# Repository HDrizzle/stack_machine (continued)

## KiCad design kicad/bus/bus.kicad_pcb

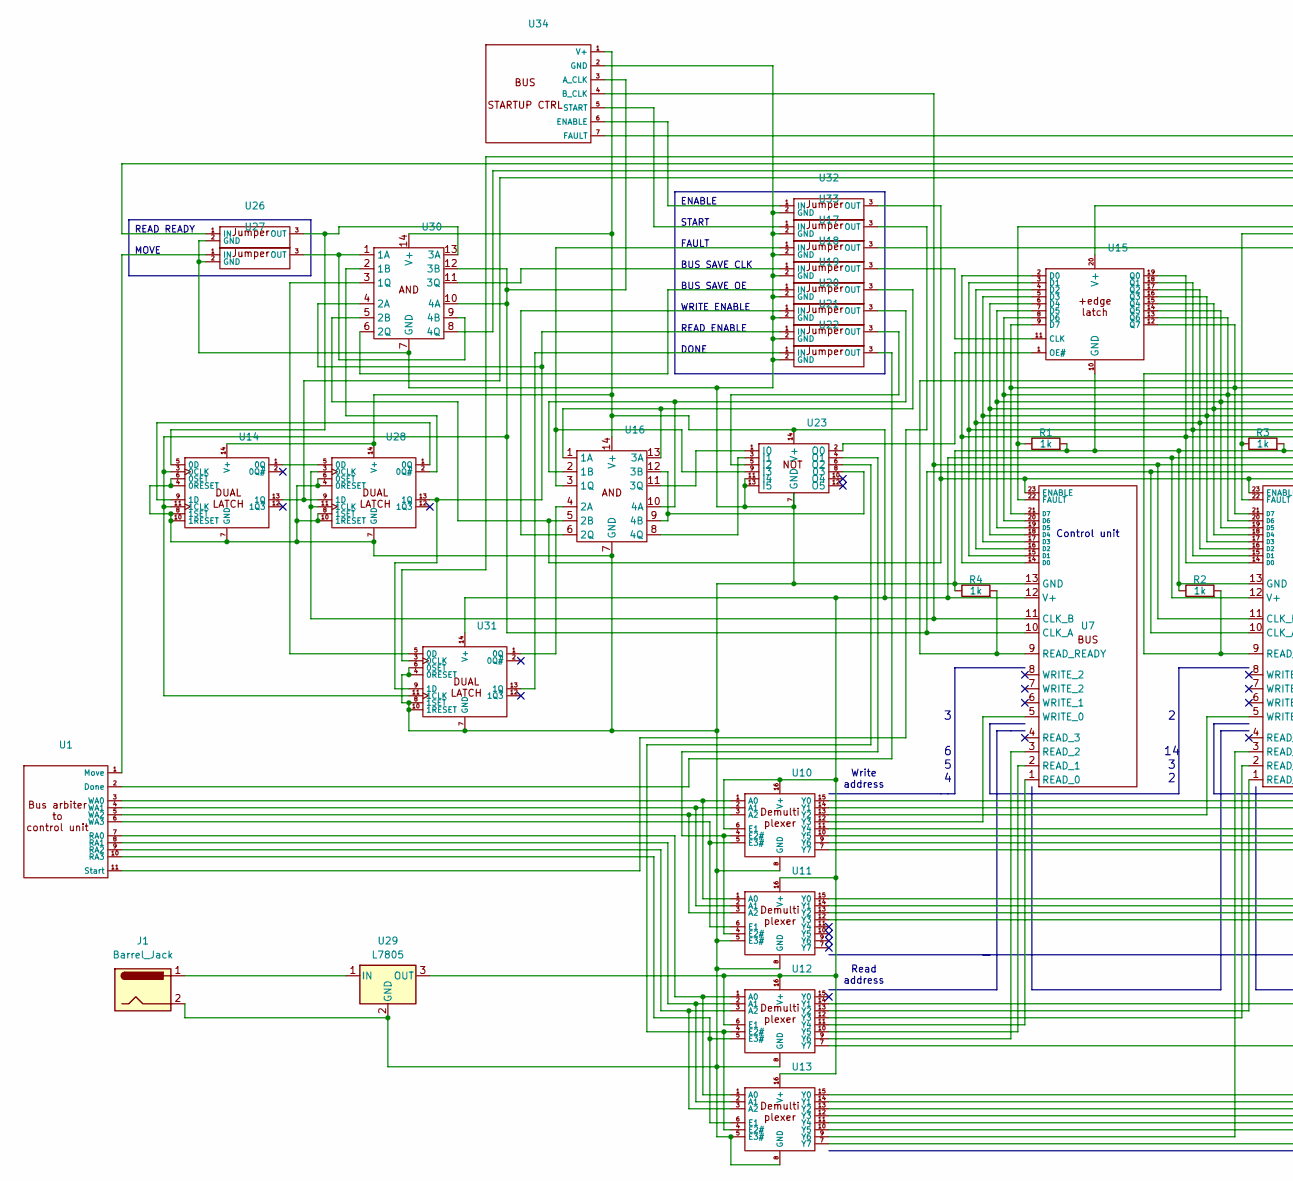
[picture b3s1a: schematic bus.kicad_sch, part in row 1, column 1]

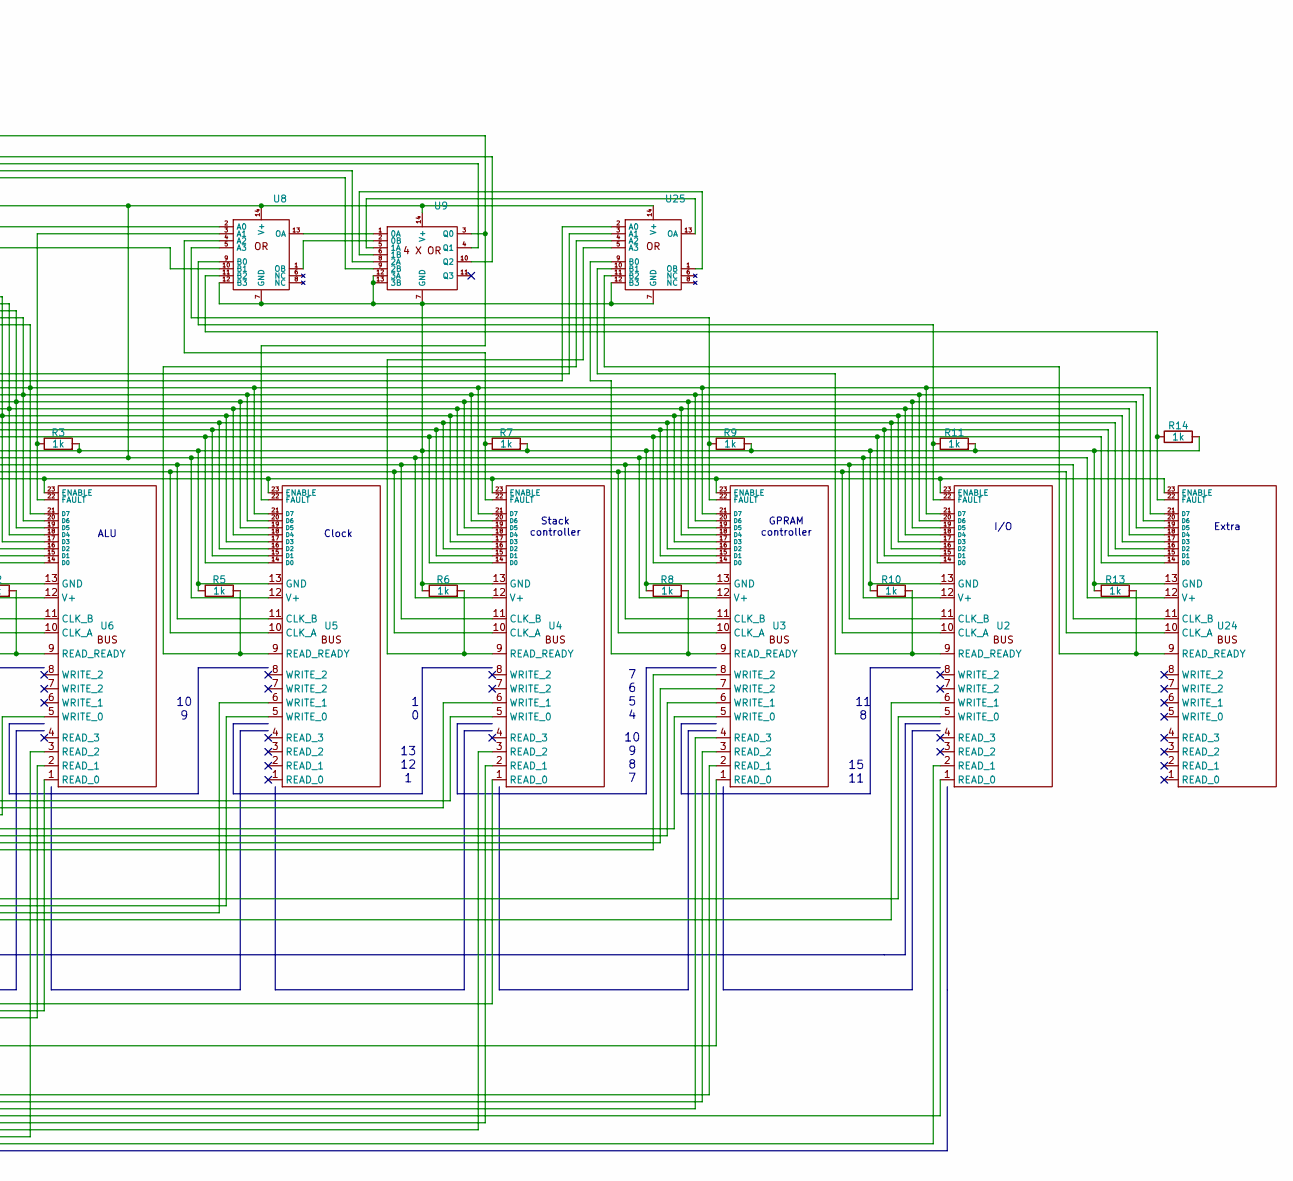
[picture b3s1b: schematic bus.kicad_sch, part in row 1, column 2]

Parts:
J1: Barrel_Jack; BarrelJack_Horizontal
R1, R2, R3, R4, R5, R6, R7, R8, R9, R10, R11, R13, R14: 1k; 0.4_pitch_resistor
U1: PinHeader_1x11_P2.54mm_Vertical
U2, U3, U4, U5, U6, U7, U24: PinHeader_1x23_P2.54mm_Vertical
U8, U9, U14, U16, U23, U25, U28, U30, U31: DIP-14_W7.62mm
U10, U11, U12, U13: DIP-16_W7.62mm
U15: DIP-20_W7.62mm
U17, U18, U19, U20, U21, U22, U26, U27, U32, U33: jumper
U29: L7805; TO-220-3_Vertical
U34: PinHeader_1x07_P2.54mm_Vertical

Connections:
unnamed: U1.2 (Done), U22.3 (OUT)
unnamed: U1.1 (Move), U27.1 (IN)
unnamed: U1.7 (RA0), U12.1 (A0), U13.1 (A0)
unnamed: U1.8 (RA1), U12.2 (A1), U13.2 (A1)
unnamed: U1.9 (RA2), U12.3 (A2), U13.3 (A2)
unnamed: U1.10 (RA3), U12.5 (E3#), U13.6 (E1)
unnamed: U1.11 (Start), U33.3 (OUT)
unnamed: U1.3 (WA0), U10.1 (A0), U11.1 (A0)
unnamed: U1.4 (WA1), U10.2 (A1), U11.2 (A1)
unnamed: U1.5 (WA2), U10.3 (A2), U11.3 (A2)
unnamed: U1.6 (WA3), U10.5 (E3#), U11.6 (E1)
unnamed: U2.11 (CLK_B), U3.11 (CLK_B), U4.11 (CLK_B), U5.11 (CLK_B), U6.11 (CLK_B), U7.11 (CLK_B), U24.11 (CLK_B), U28.3 (0CLK), U28.11 (1CLK), U34.4 (B_CLK)
unnamed: R11.1, U2.22 (FAULT), U8.9 (B0)
unnamed: R10.2, U2.9 (READ_READY), U25.10 (B1)
unnamed: R9.1, U3.22 (FAULT), U8.5 (A3)
unnamed: R7.1, U4.22 (FAULT), U8.4 (A2)
unnamed: R3.1, U6.22 (FAULT), U8.3 (A1)
unnamed: R1.1, U7.22 (FAULT), U8.2 (A0)
unnamed: U8.13 (OA), U9.1 (0A)
unnamed: U8.1 (OB), U9.2 (0B)
unnamed: U2.12 (V+), U3.12 (V+), U4.12 (V+), U5.12 (V+), U6.12 (V+), U7.12 (V+), U8.14 (V+), U9.14 (V+), U10.6 (E1), U10.16 (V+), U11.16 (V+), U12.6 (E1), U12.16 (V+), U13.16 (V+), U14.14 (V+), U15.20 (V+), U16.14 (V+), U23.14 (V+), U24.12 (V+), U25.14 (V+), U28.14 (V+), U29.3 (OUT), U30.14 (V+), U31.14 (V+), U34.1 (V+)
unnamed: U10.4 (E2#), U11.4 (E2#), U23.4 (O1)
unnamed: J1.2, R1.2, R2.1, R3.2, R4.1, R5.1, R6.1, R7.2, R8.1, R9.2, R10.1, R11.2, R13.1, R14.2, U2.13 (GND), U3.13 (GND), U4.13 (GND), U5.13 (GND), U6.13 (GND), U7.13 (GND), U8.7 (GND), U8.12 (B3), U9.7 (GND), U9.12 (3A), U9.13 (3B), U10.8 (GND), U11.5 (E3#), U11.8 (GND), U12.8 (GND), U13.5 (E3#), U13.8 (GND), U14.4 (0RESET), U14.6 (0SET), U14.7 (GND), U14.8 (1SET), U14.10 (1RESET), U15.10 (GND), U16.7 (GND), U17.2 (GND), U18.2 (GND), U19.2 (GND), U20.2 (GND), U21.2 (GND), U22.2 (GND), U23.7 (GND), U23.11 (I4), U23.13 (I5), U24.13 (GND), U25.7 (GND), U25.12 (B3), U26.2 (GND), U27.2 (GND), U28.4 (0RESET), U28.6 (0SET), U28.7 (GND), U28.8 (1SET), U28.10 (1RESET), U29.2 (GND), U30.7 (GND), U31.4 (0RESET), U31.6 (0SET), U31.7 (GND), U31.8 (1SET), U31.10 (1RESET), U32.2 (GND), U33.2 (GND), U34.2 (GND)
unnamed: U4.5 (WRITE_0), U10.15 (Y0)
unnamed: U4.6 (WRITE_1), U10.14 (Y1)
unnamed: U6.5 (WRITE_0), U10.13 (Y2)
unnamed: U7.5 (WRITE_0), U10.12 (Y3)
unnamed: U3.5 (WRITE_0), U10.11 (Y4)
unnamed: U3.6 (WRITE_1), U10.10 (Y5)
unnamed: U3.7 (WRITE_2), U10.9 (Y6)
unnamed: U3.8 (WRITE_2), U10.7 (Y7)
unnamed: U2.5 (WRITE_0), U11.15 (Y0)
unnamed: U5.5 (WRITE_0), U11.14 (Y1)
unnamed: U5.6 (WRITE_1), U11.13 (Y2)
unnamed: U2.6 (WRITE_1), U11.12 (Y3)
unnamed: U12.4 (E2#), U13.4 (E2#), U23.6 (O2)
unnamed: U4.1 (READ_0), U12.14 (Y1)
unnamed: U6.1 (READ_0), U12.13 (Y2)
unnamed: U6.2 (READ_1), U12.12 (Y3)
unnamed: U7.1 (READ_0), U12.11 (Y4)
unnamed: U7.2 (READ_1), U12.10 (Y5)
unnamed: U7.3 (READ_2), U12.9 (Y6)
unnamed: U3.1 (READ_0), U12.7 (Y7)
unnamed: U3.2 (READ_1), U13.15 (Y0)
unnamed: U3.3 (READ_2), U13.14 (Y1)
unnamed: U3.4 (READ_3), U13.13 (Y2)
unnamed: U2.1 (READ_0), U13.12 (Y3)
unnamed: U4.2 (READ_1), U13.11 (Y4)
unnamed: U4.3 (READ_2), U13.10 (Y5)
unnamed: U6.3 (READ_2), U13.9 (Y6)
unnamed: U2.2 (READ_1), U13.7 (Y7)
unnamed: U2.10 (CLK_A), U3.10 (CLK_A), U4.10 (CLK_A), U5.10 (CLK_A), U6.10 (CLK_A), U7.10 (CLK_A), U14.3 (0CLK), U14.11 (1CLK), U24.10 (CLK_A), U30.10 (4A), U30.12 (3B), U31.11 (1CLK), U34.3 (A_CLK)
unnamed: U14.5 (0D), U26.3 (OUT), U30.13 (3A)
unnamed: U14.1 (0Q), U28.5 (0D)
unnamed: U14.9 (1D), U28.1 (0Q)
unnamed: U9.9 (2B), U14.13 (1Q), U28.9 (1D)
unnamed: U15.11 (CLK), U18.3 (OUT)
unnamed: U2.14 (D0), U3.14 (D0), U4.14 (D0), U5.14 (D0), U6.14 (D0), U7.14 (D0), U15.2 (D0), U15.19 (Q0), U24.14 (D0)
unnamed: U2.15 (D1), U3.15 (D1), U4.15 (D1), U5.15 (D1), U6.15 (D1), U7.15 (D1), U15.3 (D1), U15.18 (Q1), U24.15 (D1)
unnamed: U2.16 (D2), U3.16 (D2), U4.16 (D2), U5.16 (D2), U6.16 (D2), U7.16 (D2), U15.4 (D2), U15.17 (Q2), U24.16 (D2)
unnamed: U2.17 (D3), U3.17 (D3), U4.17 (D3), U5.17 (D3), U6.17 (D3), U7.17 (D3), U15.5 (D3), U15.16 (Q3), U24.17 (D3)
unnamed: U2.18 (D4), U3.18 (D4), U4.18 (D4), U5.18 (D4), U6.18 (D4), U7.18 (D4), U15.6 (D4), U15.15 (Q4), U24.18 (D4)
unnamed: U2.19 (D5), U3.19 (D5), U4.19 (D5), U5.19 (D5), U6.19 (D5), U7.19 (D5), U15.7 (D5), U15.14 (Q5), U24.19 (D5)
unnamed: U2.20 (D6), U3.20 (D6), U4.20 (D6), U5.20 (D6), U6.20 (D6), U7.20 (D6), U15.8 (D6), U15.13 (Q6), U24.20 (D6)
unnamed: U2.21 (D7), U3.21 (D7), U4.21 (D7), U5.21 (D7), U6.21 (D7), U7.21 (D7), U15.9 (D7), U15.12 (Q7), U24.21 (D7)
unnamed: U15.1 (OE#), U23.2 (O0)
unnamed: U16.1 (1A), U16.13 (3A), U19.3 (OUT)
unnamed: U16.2 (1B), U16.10 (4A), U20.3 (OUT)
unnamed: U16.3 (1Q), U17.1 (IN), U23.9 (I3)
unnamed: U16.4 (2A), U31.1 (0Q)
unnamed: U2.23 (ENABLE), U3.23 (ENABLE), U4.23 (ENABLE), U5.23 (ENABLE), U6.23 (ENABLE), U7.23 (ENABLE), U16.5 (2B), U24.23 (ENABLE), U30.5 (2B), U32.3 (OUT)
unnamed: U16.6 (2Q), U20.1 (IN)
unnamed: U16.9 (4B), U16.12 (3B), U23.8 (03)
unnamed: U16.11 (3Q), U23.1 (I0)
unnamed: U16.8 (4Q), U23.3 (I1)
unnamed: U8.10 (B1), U17.3 (OUT)
unnamed: U18.1 (IN), U30.11 (3Q)
unnamed: U19.1 (IN), U30.6 (2Q)
unnamed: U21.1 (IN), U28.13 (1Q), U30.4 (2A), U31.9 (1D)
unnamed: U21.3 (OUT), U23.5 (I2)
unnamed: U22.1 (IN), U31.13 (1Q)
unnamed: R14.1, U8.11 (B2), U24.22 (FAULT)
unnamed: R13.2, U24.9 (READ_READY), U25.11 (B2)
unnamed: R4.2, U7.9 (READ_READY), U25.2 (A0)
unnamed: R2.2, U6.9 (READ_READY), U25.3 (A1)
unnamed: R5.2, U5.9 (READ_READY), U25.4 (A2)
unnamed: R6.2, U4.9 (READ_READY), U25.5 (A3)
unnamed: R8.2, U3.9 (READ_READY), U25.9 (B0)
unnamed: U9.5 (1A), U25.13 (OA)
unnamed: U9.6 (1B), U25.1 (OB)
unnamed: U9.4 (Q1), U26.1 (IN)
unnamed: U27.3 (OUT), U30.1 (1A), U30.9 (4B)
unnamed: U28.2 (0Q#), U30.2 (1B)
unnamed: J1.1, U29.1 (IN)
unnamed: U30.3 (1Q), U31.5 (0D)
unnamed: U9.8 (2A), U30.8 (4Q)
unnamed: U9.10 (Q2), U31.3 (0CLK)
unnamed: U32.1 (IN), U34.6 (ENABLE)
unnamed: U33.1 (IN), U34.5 (START)
unnamed: U5.22 (FAULT), U9.3 (Q0), U34.7 (FAULT)

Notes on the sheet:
READ READY MOVE
ENABLE START FAULT BUS SAVE CLK BUS SAVE OE WRITE ENABLE READ ENABLE DONE
14 3 2
ALU
I/O
Read address
GPRAM controller
Control unit
6 5 4
13 12 1
10 9 8 7
7 6 5 4
11 8
Clock
Stack controller
1 0
Write address
10 9
Extra
15 11

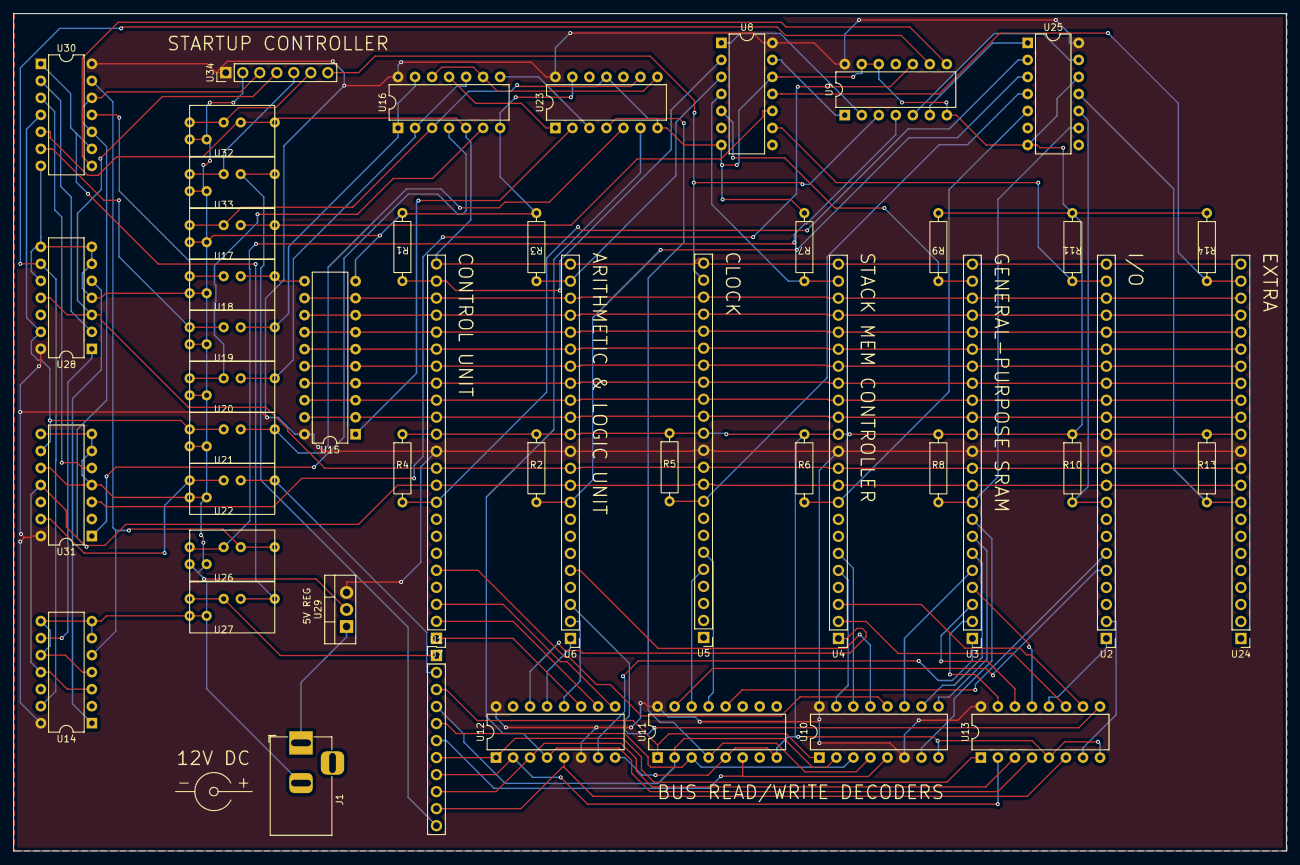
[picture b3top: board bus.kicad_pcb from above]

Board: 2 copper layers, 190.0 x 125.0 mm, 48 parts (0 on the bottom side), 100 nets.

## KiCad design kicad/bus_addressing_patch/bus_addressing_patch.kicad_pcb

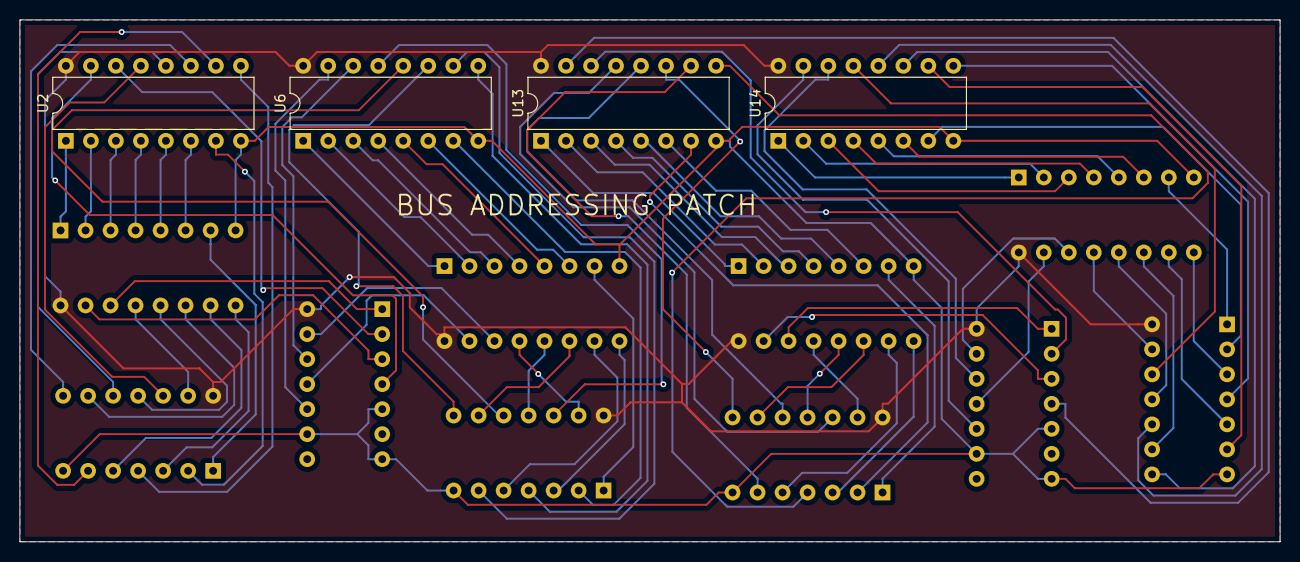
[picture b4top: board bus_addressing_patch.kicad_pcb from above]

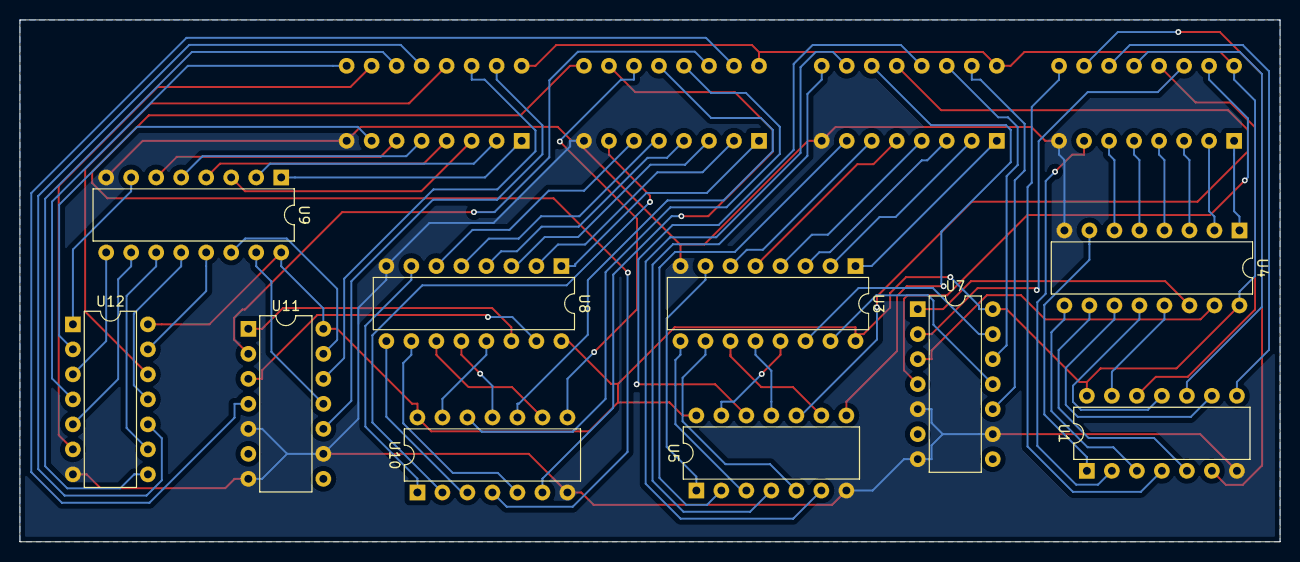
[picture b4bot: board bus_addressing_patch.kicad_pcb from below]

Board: 2 copper layers, 128.0 x 53.0 mm, 14 parts (10 on the bottom side), 90 nets.

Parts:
U1, U5, U7, U10, U11, U12: DIP-14_W7.62mm
U2, U3, U4, U6, U8, U9, U13, U14: DIP-16_W7.62mm

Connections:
unnamed: U1.8 (03), U2.11 (Y4)
unnamed: U1.7 (GND), U2.8 (GND), U3.8 (GND), U4.8 (GND), U5.7 (GND), U6.8 (GND), U7.5 (I2), U7.7 (GND), U7.9 (I3), U8.8 (GND), U9.8 (GND), U10.7 (GND), U11.5 (I2), U11.7 (GND), U11.9 (I3), U12.7 (GND), U13.8 (GND), U14.8 (GND)
unnamed: U1.1 (I0), U4.7 (Y7)
unnamed: U1.3 (I1), U4.9 (Y6)
unnamed: U1.5 (I2), U4.10 (Y5)
unnamed: U1.9 (I3), U4.11 (Y4)
unnamed: U1.11 (I4), U4.12 (Y3)
unnamed: U1.13 (I5), U4.13 (Y2)
unnamed: U1.2 (O0), U2.7 (Y7)
unnamed: U1.4 (O1), U2.9 (Y6)
unnamed: U1.6 (O2), U2.10 (Y5)
unnamed: U1.10 (O4), U2.12 (Y3)
unnamed: U1.12 (O5), U2.13 (Y2)
unnamed: U1.14 (V+), U2.16 (V+), U3.16 (V+), U4.16 (V+), U5.14 (V+), U6.16 (V+), U7.14 (V+), U8.16 (V+), U9.16 (V+), U10.14 (V+), U11.14 (V+), U12.14 (V+), U13.16 (V+), U14.16 (V+)
unnamed: U2.1 (A0), U4.1 (A0)
unnamed: U2.2 (A1), U4.2 (A1)
unnamed: U2.3 (A2), U4.3 (A2)
unnamed: U2.6 (E1), U4.6 (E1)
unnamed: U2.4 (E2#), U4.4 (E2#)
unnamed: U2.5 (E3#), U4.5 (E3#)
unnamed: U2.15 (Y0), U7.4 (O1)
unnamed: U2.14 (Y1), U7.2 (O0)
unnamed: U3.1 (A0), U6.1 (A0)
unnamed: U3.2 (A1), U6.2 (A1)
unnamed: U3.3 (A2), U6.3 (A2)
unnamed: U3.6 (E1), U6.6 (E1)
unnamed: U3.4 (E2#), U6.4 (E2#)
unnamed: U3.5 (E3#), U6.5 (E3#)
unnamed: U3.15 (Y0), U7.11 (I4)
unnamed: U3.14 (Y1), U7.13 (I5)
unnamed: U3.13 (Y2), U5.13 (I5)
unnamed: U3.12 (Y3), U5.11 (I4)
unnamed: U3.11 (Y4), U5.9 (I3)
unnamed: U3.10 (Y5), U5.5 (I2)
unnamed: U3.9 (Y6), U5.3 (I1)
unnamed: U3.7 (Y7), U5.1 (I0)
unnamed: U4.15 (Y0), U7.3 (I1)
unnamed: U4.14 (Y1), U7.1 (I0)
unnamed: U5.8 (03), U6.11 (Y4)
unnamed: U5.2 (O0), U6.7 (Y7)
unnamed: U5.4 (O1), U6.9 (Y6)
unnamed: U5.6 (O2), U6.10 (Y5)
unnamed: U5.10 (O4), U6.12 (Y3)
unnamed: U5.12 (O5), U6.13 (Y2)
unnamed: U6.15 (Y0), U7.10 (O4)
unnamed: U6.14 (Y1), U7.12 (O5)
unnamed: U10.8 (03), U13.11 (Y4)
unnamed: U8.7 (Y7), U10.1 (I0)
unnamed: U8.9 (Y6), U10.3 (I1)
unnamed: U8.10 (Y5), U10.5 (I2)
unnamed: U8.11 (Y4), U10.9 (I3)
unnamed: U8.12 (Y3), U10.11 (I4)
unnamed: U8.13 (Y2), U10.13 (I5)
unnamed: U10.2 (O0), U13.7 (Y7)
unnamed: U10.4 (O1), U13.9 (Y6)
unnamed: U10.6 (O2), U13.10 (Y5)
unnamed: U10.10 (O4), U13.12 (Y3)
unnamed: U10.12 (O5), U13.13 (Y2)
unnamed: U8.14 (Y1), U11.1 (I0)
unnamed: U8.15 (Y0), U11.3 (I1)
unnamed: U9.15 (Y0), U11.11 (I4)
unnamed: U9.14 (Y1), U11.13 (I5)
unnamed: U11.2 (O0), U13.14 (Y1)
unnamed: U11.4 (O1), U13.15 (Y0)
unnamed: U11.10 (O4), U14.15 (Y0)
unnamed: U11.12 (O5), U14.14 (Y1)
unnamed: U12.8 (03), U14.11 (Y4)
unnamed: U9.7 (Y7), U12.1 (I0)
unnamed: U9.9 (Y6), U12.3 (I1)
unnamed: U9.10 (Y5), U12.5 (I2)
unnamed: U9.11 (Y4), U12.9 (I3)
unnamed: U9.12 (Y3), U12.11 (I4)
unnamed: U9.13 (Y2), U12.13 (I5)
unnamed: U12.2 (O0), U14.7 (Y7)
unnamed: U12.4 (O1), U14.9 (Y6)
unnamed: U12.6 (O2), U14.10 (Y5)
unnamed: U12.10 (O4), U14.12 (Y3)
unnamed: U12.12 (O5), U14.13 (Y2)
unnamed: U8.1 (A0), U13.1 (A0)
unnamed: U8.2 (A1), U13.2 (A1)
unnamed: U8.3 (A2), U13.3 (A2)
unnamed: U8.6 (E1), U13.6 (E1)
unnamed: U8.4 (E2#), U13.4 (E2#)
unnamed: U8.5 (E3#), U13.5 (E3#)
unnamed: U9.1 (A0), U14.1 (A0)
unnamed: U9.2 (A1), U14.2 (A1)
unnamed: U9.3 (A2), U14.3 (A2)
unnamed: U9.6 (E1), U14.6 (E1)
unnamed: U9.4 (E2#), U14.4 (E2#)
unnamed: U9.5 (E3#), U14.5 (E3#)

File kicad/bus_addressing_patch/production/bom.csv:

Designator,Footprint,Quantity,Value,LCSC Part #
"U1, U10, U11, U12, U5, U7",DIP-14_W7.62mm,6,~,
"U13, U14, U2, U3, U4, U6, U8, U9",DIP-16_W7.62mm,8,~,

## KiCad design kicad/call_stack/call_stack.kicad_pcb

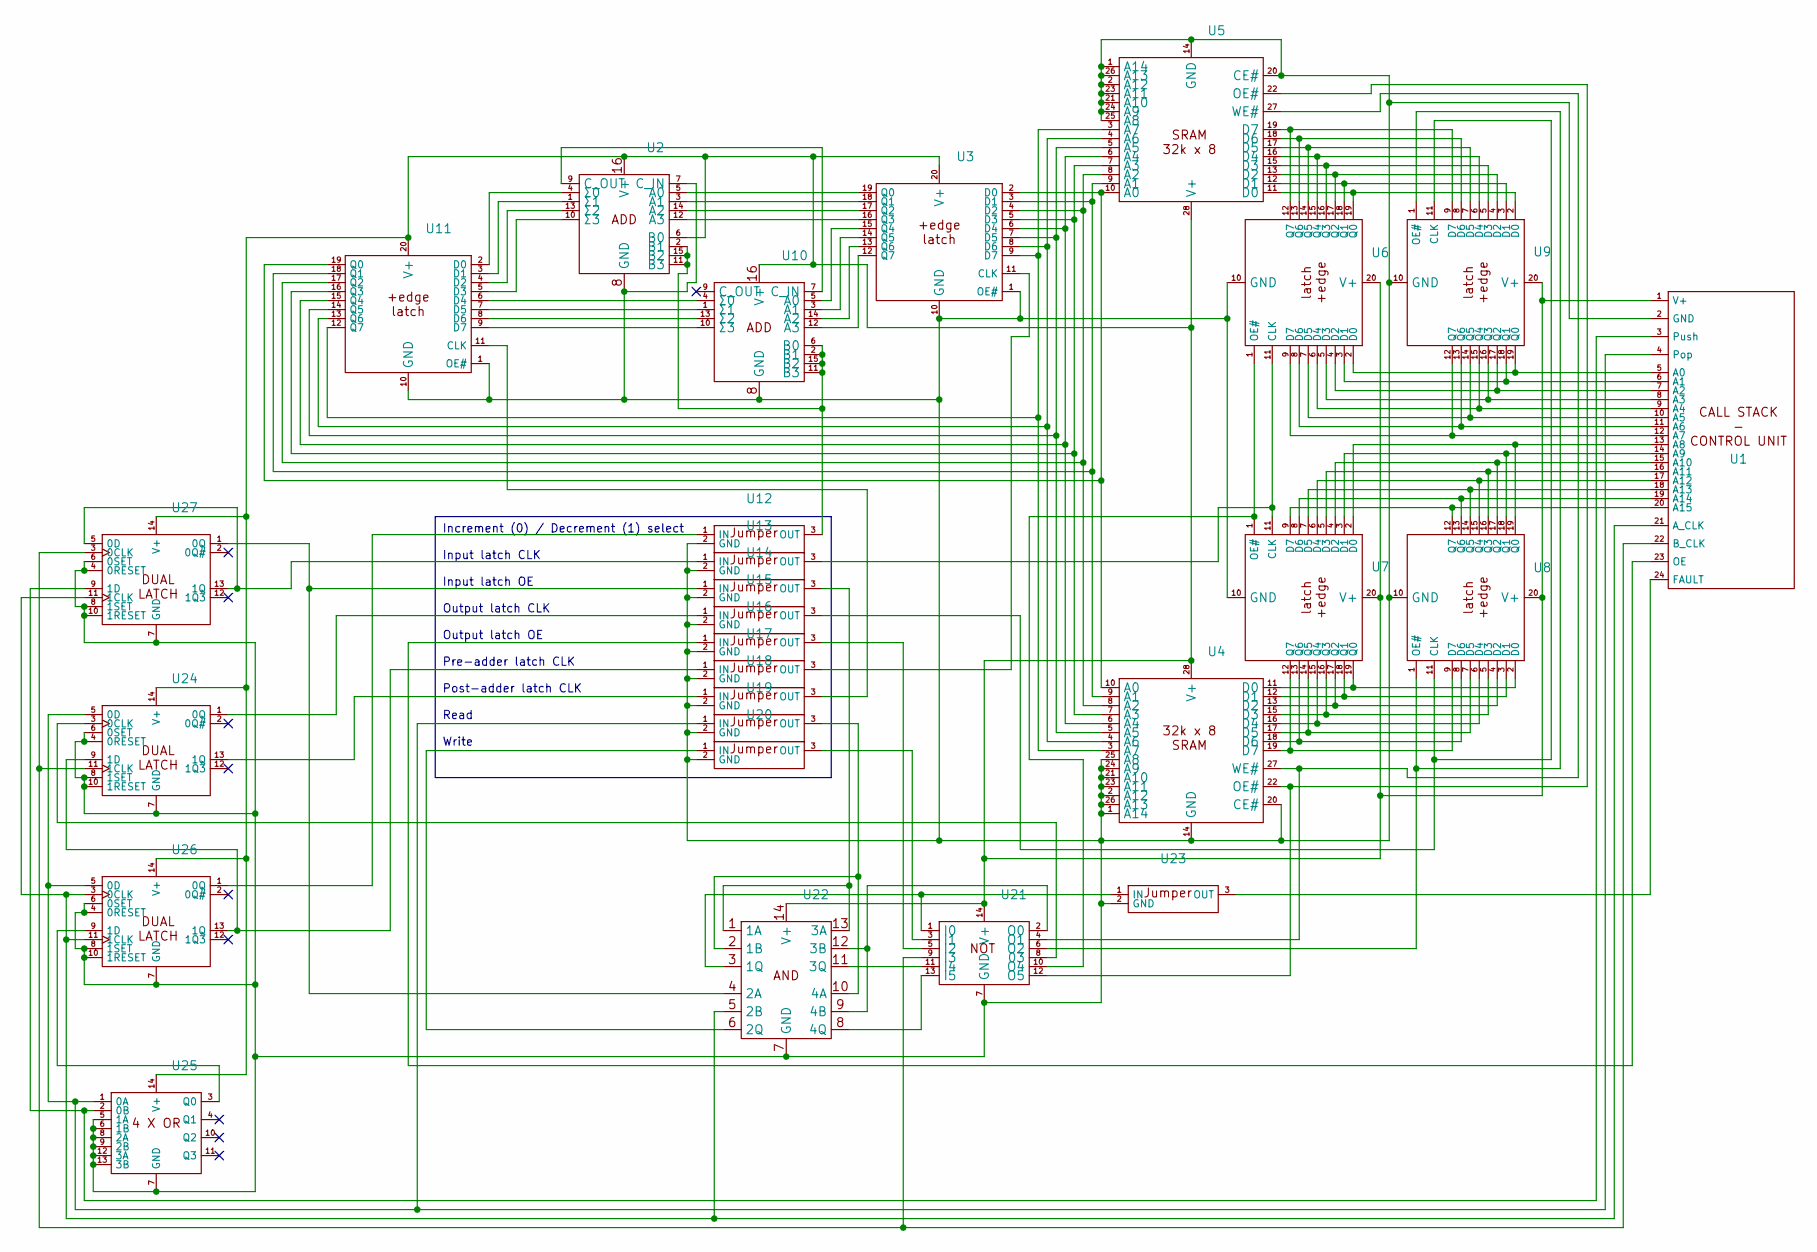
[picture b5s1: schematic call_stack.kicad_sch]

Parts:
U1: PinHeader_1x24_P2.54mm_Vertical
U2, U10: DIP-16_W7.62mm
U3, U6, U7, U8, U9, U11: DIP-20_W7.62mm
U4, U5: DIP-28_W15.24mm
U12, U13, U14, U15, U16, U17, U18, U19, U20, U23: jumper
U21, U22, U24, U25, U26, U27: DIP-14_W7.62mm

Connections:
unnamed: U1.5 (A0), U6.2 (D0), U9.19 (Q0)
unnamed: U1.6 (A1), U6.3 (D1), U9.18 (Q1)
unnamed: U1.7 (A2), U6.4 (D2), U9.17 (Q2)
unnamed: U1.8 (A3), U6.5 (D3), U9.16 (Q3)
unnamed: U1.9 (A4), U6.6 (D4), U9.15 (Q4)
unnamed: U1.10 (A5), U6.7 (D5), U9.14 (Q5)
unnamed: U1.11 (A6), U6.8 (D6), U9.13 (Q6)
unnamed: U1.12 (A7), U6.9 (D7), U9.12 (Q7)
unnamed: U1.13 (A8), U7.2 (D0), U8.19 (Q0)
unnamed: U1.14 (A9), U7.3 (D1), U8.18 (Q1)
unnamed: U1.15 (A10), U7.4 (D2), U8.17 (Q2)
unnamed: U1.16 (A11), U7.5 (D3), U8.16 (Q3)
unnamed: U1.17 (A12), U7.6 (D4), U8.15 (Q4)
unnamed: U1.18 (A13), U7.7 (D5), U8.14 (Q5)
unnamed: U1.19 (A14), U7.8 (D6), U8.13 (Q6)
unnamed: U1.20 (A15), U7.9 (D7), U8.12 (Q7)
unnamed: U1.21 (A_CLK), U22.5 (2B), U26.3 (0CLK), U26.11 (1CLK), U27.11 (1CLK)
unnamed: U1.22 (B_CLK), U21.9 (I3), U24.11 (1CLK), U27.3 (0CLK)
unnamed: U1.24 (FAULT), U23.3 (OUT)
unnamed: U1.2 (GND), U2.7 (C_IN), U2.8 (GND), U3.1 (OE#), U3.10 (GND), U4.1 (A14), U4.2 (A12), U4.14 (GND), U4.20 (CE#), U4.21 (A10), U4.23 (A11), U4.24 (A9), U4.25 (A8), U4.26 (A13), U5.1 (A14), U5.2 (A12), U5.14 (GND), U5.20 (CE#), U5.21 (A10), U5.23 (A11), U5.24 (A9), U5.25 (A8), U5.26 (A13), U6.10 (GND), U7.10 (GND), U8.10 (GND), U9.10 (GND), U10.8 (GND), U11.1 (OE#), U11.10 (GND), U12.2 (GND), U13.2 (GND), U14.2 (GND), U15.2 (GND), U16.2 (GND), U17.2 (GND), U18.2 (GND), U19.2 (GND), U20.2 (GND), U21.7 (GND), U22.7 (GND), U23.2 (GND), U24.4 (0RESET), U24.6 (0SET), U24.7 (GND), U24.8 (1SET), U24.10 (1RESET), U25.5 (1A), U25.6 (1B), U25.7 (GND), U25.8 (2A), U25.9 (2B), U25.12 (3A), U25.13 (3B), U26.4 (0RESET), U26.6 (0SET), U26.7 (GND), U26.8 (1SET), U26.10 (1RESET), U27.4 (0RESET), U27.6 (0SET), U27.7 (GND), U27.8 (1SET), U27.10 (1RESET)
unnamed: U1.23 (OE), U16.1 (IN)
unnamed: U1.4 (Pop), U19.1 (IN), U24.5 (0D), U25.1 (0A), U26.5 (0D)
unnamed: U1.3 (Push), U25.2 (0B), U27.9 (1D)
unnamed: U1.1 (V+), U2.6 (B0), U2.16 (V+), U3.20 (V+), U4.28 (V+), U5.28 (V+), U6.20 (V+), U7.20 (V+), U8.20 (V+), U9.20 (V+), U10.16 (V+), U11.20 (V+), U21.14 (V+), U22.14 (V+), U24.14 (V+), U25.14 (V+), U26.14 (V+), U27.14 (V+)
unnamed: U2.5 (A0), U3.19 (Q0)
unnamed: U2.3 (A1), U3.18 (Q1)
unnamed: U2.14 (A2), U3.17 (Q2)
unnamed: U2.12 (A3), U3.16 (Q3)
unnamed: U4.11 (D0), U7.19 (Q0), U8.2 (D0)
unnamed: U4.12 (D1), U7.18 (Q1), U8.3 (D1)
unnamed: U4.13 (D2), U7.17 (Q2), U8.4 (D2)
unnamed: U4.15 (D3), U7.16 (Q3), U8.5 (D3)
unnamed: U4.16 (D4), U7.15 (Q4), U8.6 (D4)
unnamed: U4.17 (D5), U7.14 (Q5), U8.7 (D5)
unnamed: U4.18 (D6), U7.13 (Q6), U8.8 (D6)
unnamed: U4.19 (D7), U7.12 (Q7), U8.9 (D7)
unnamed: U5.11 (D0), U6.19 (Q0), U9.2 (D0)
unnamed: U5.12 (D1), U6.18 (Q1), U9.3 (D1)
unnamed: U5.13 (D2), U6.17 (Q2), U9.4 (D2)
unnamed: U5.15 (D3), U6.16 (Q3), U9.5 (D3)
unnamed: U5.16 (D4), U6.15 (Q4), U9.6 (D4)
unnamed: U5.17 (D5), U6.14 (Q5), U9.7 (D5)
unnamed: U5.18 (D6), U6.13 (Q6), U9.8 (D6)
unnamed: U5.19 (D7), U6.12 (Q7), U9.9 (D7)
unnamed: U3.15 (Q4), U10.5 (A0)
unnamed: U3.14 (Q5), U10.3 (A1)
unnamed: U3.13 (Q6), U10.14 (A2)
unnamed: U3.12 (Q7), U10.12 (A3)
unnamed: U2.2 (B1), U2.11 (B3), U2.15 (B2), U10.2 (B1), U10.6 (B0), U10.11 (B3), U10.15 (B2), U12.3 (OUT)
unnamed: U2.9 (C_OUT), U10.7 (C_IN)
unnamed: U10.4 (Σ0), U11.6 (D4)
unnamed: U10.1 (Σ1), U11.7 (D5)
unnamed: U10.13 (Σ2), U11.8 (D6)
unnamed: U10.10 (Σ3), U11.9 (D7)
unnamed: U11.11 (CLK), U18.3 (OUT)
unnamed: U2.4 (Σ0), U11.2 (D0)
unnamed: U2.1 (Σ1), U11.3 (D1)
unnamed: U2.13 (Σ2), U11.4 (D2)
unnamed: U2.10 (Σ3), U11.5 (D3)
unnamed: U3.2 (D0), U4.10 (A0), U5.10 (A0), U11.19 (Q0)
unnamed: U3.3 (D1), U4.9 (A1), U5.9 (A1), U11.18 (Q1)
unnamed: U3.4 (D2), U4.8 (A2), U5.8 (A2), U11.17 (Q2)
unnamed: U3.5 (D3), U4.7 (A3), U5.7 (A3), U11.16 (Q3)
unnamed: U3.6 (D4), U4.6 (A4), U5.6 (A4), U11.15 (Q4)
unnamed: U3.7 (D5), U4.5 (A5), U5.5 (A5), U11.14 (Q5)
unnamed: U3.8 (D6), U4.4 (A6), U5.4 (A6), U11.13 (Q6)
unnamed: U3.9 (D7), U4.3 (A7), U5.3 (A7), U11.12 (Q7)
unnamed: U12.1 (IN), U26.1 (0Q)
unnamed: U13.1 (IN), U27.5 (0D), U27.13 (1Q)
unnamed: U6.11 (CLK), U7.11 (CLK), U13.3 (OUT)
unnamed: U14.1 (IN), U22.4 (2A), U27.1 (0Q)
unnamed: U14.3 (OUT), U22.1 (1A), U22.13 (3A)
unnamed: U15.1 (IN), U24.1 (0Q)
unnamed: U8.11 (CLK), U9.11 (CLK), U15.3 (OUT)
unnamed: U16.3 (OUT), U21.5 (I2)
unnamed: U17.1 (IN), U24.9 (1D), U26.13 (1Q)
unnamed: U3.11 (CLK), U17.3 (OUT)
unnamed: U18.1 (IN), U24.13 (1Q)
unnamed: U19.3 (OUT), U22.2 (1B), U22.10 (4A)
unnamed: U20.1 (IN), U22.6 (2Q)
unnamed: U20.3 (OUT), U21.3 (I1)
unnamed: U21.8 (03), U24.3 (0CLK)
unnamed: U21.1 (I0), U22.3 (1Q), U23.1 (IN)
unnamed: U21.11 (I4), U22.11 (3Q)
unnamed: U21.13 (I5), U22.8 (4Q)
unnamed: U21.2 (O0), U22.9 (4B), U22.12 (3B)
unnamed: U4.27 (WE#), U5.27 (WE#), U21.4 (O1)
unnamed: U8.1 (OE#), U9.1 (OE#), U21.6 (O2)
unnamed: U6.1 (OE#), U7.1 (OE#), U21.10 (O4)
unnamed: U4.22 (OE#), U5.22 (OE#), U21.12 (O5)
unnamed: U25.3 (Q0), U26.9 (1D)

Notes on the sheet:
Increment (0) / Decrement (1) select Input latch CLK Input latch OE Output latch CLK Output latch OE Pre-adder latch CLK Post-adder latch CLK Read Write

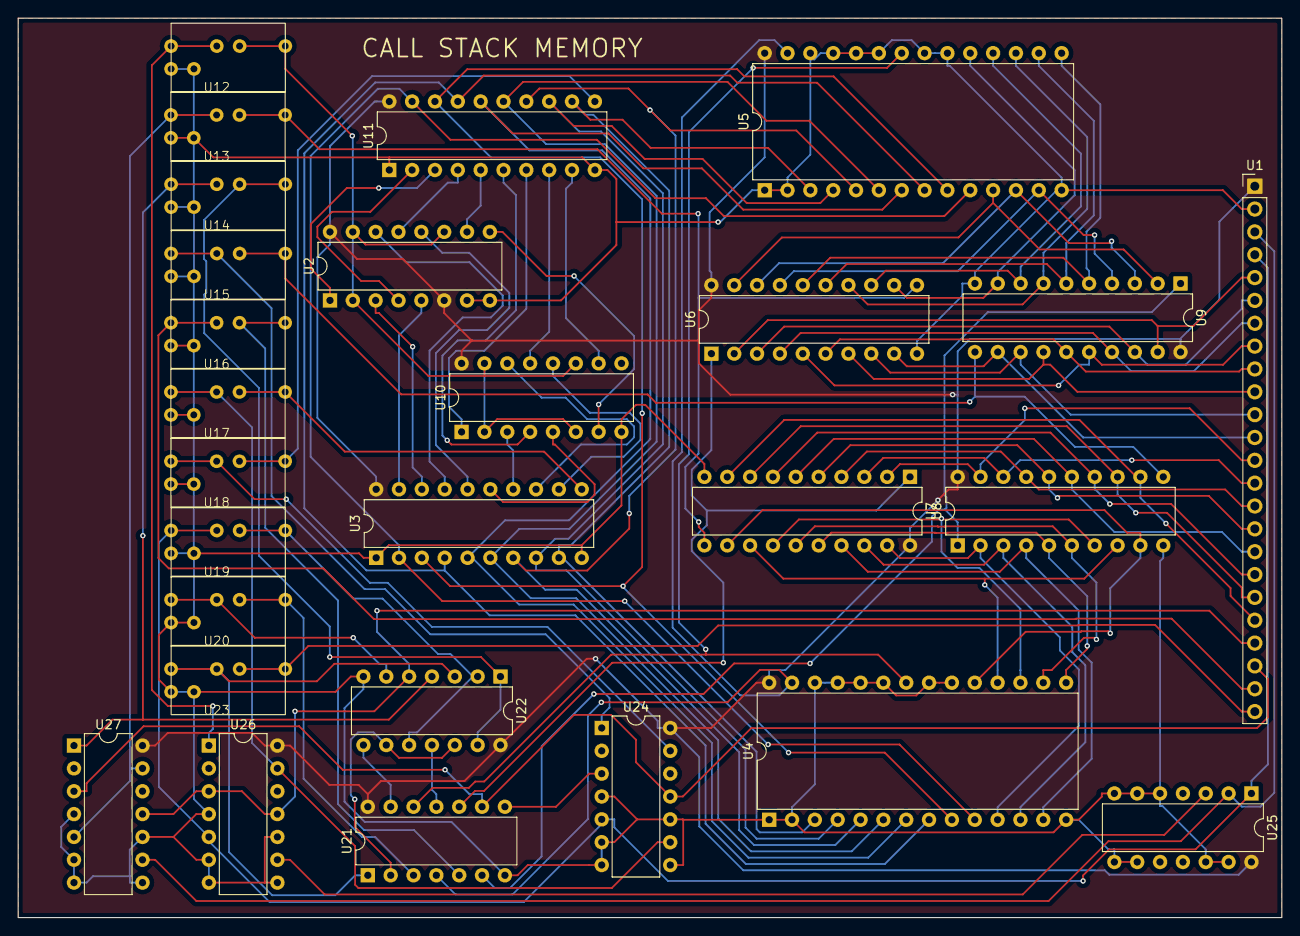
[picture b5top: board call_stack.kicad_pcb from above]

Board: 2 copper layers, 140.5 x 100.0 mm, 27 parts (0 on the bottom side), 91 nets.
